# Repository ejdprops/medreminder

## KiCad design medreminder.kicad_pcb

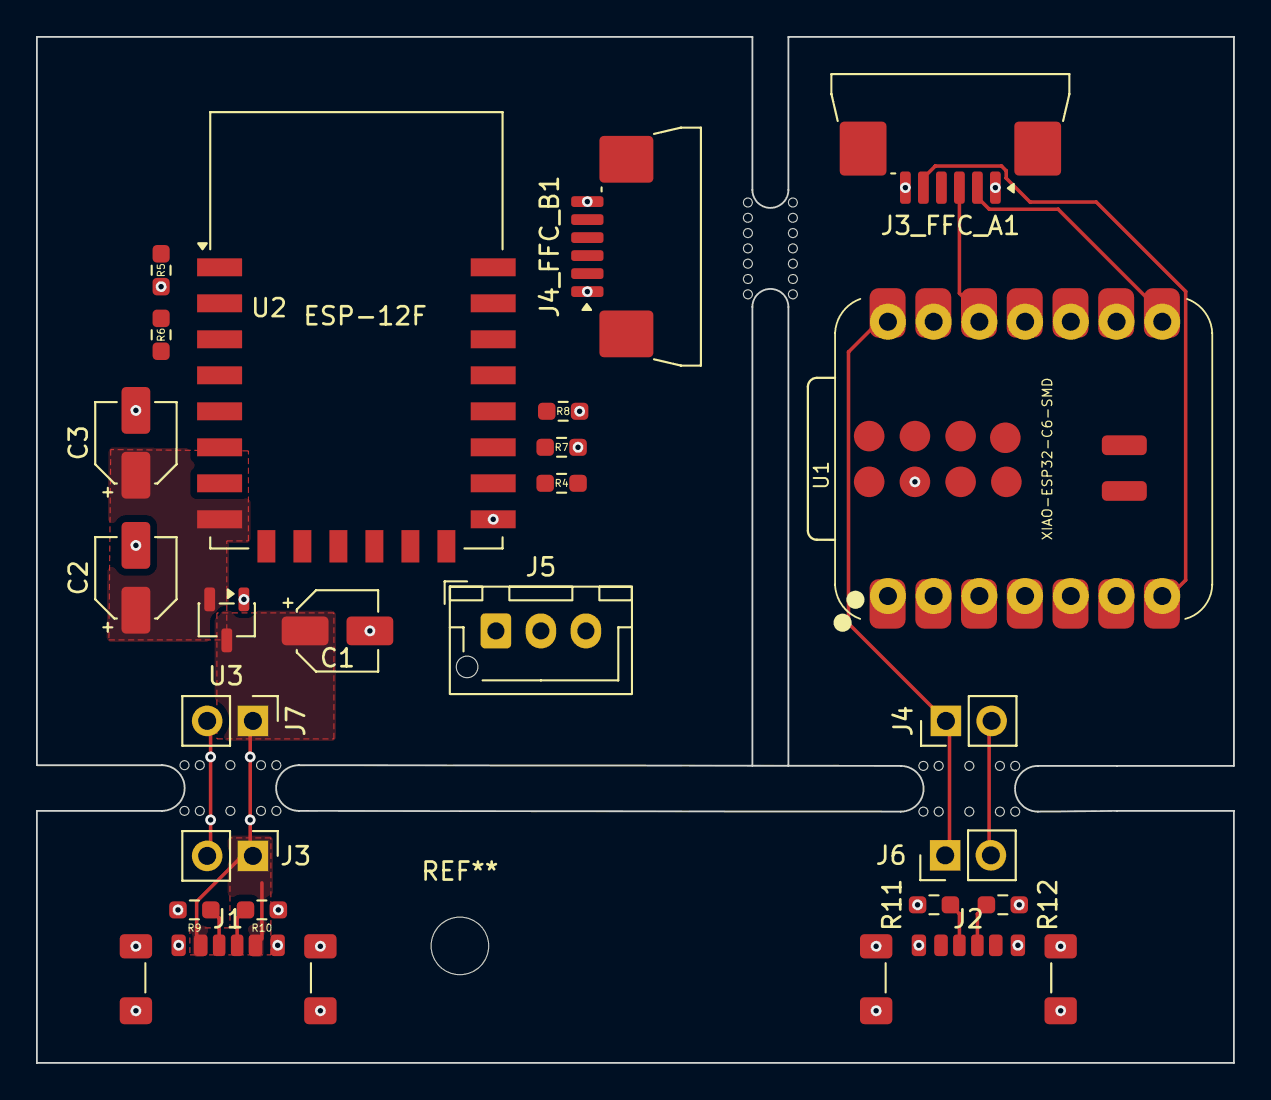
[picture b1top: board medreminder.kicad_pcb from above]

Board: 2 copper layers, 66.5 x 57.0 mm, 24 parts (0 on the bottom side), 16 nets.

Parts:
C1, C3: 10uF; CP_Elec_4x5.4
C2: 100nF; CP_Elec_4x5.4
J1: USB_C PWR XIAO (SNAP); USB_C_Receptacle_GCT_USB4135-GF-A_6P_TopMnt_Horizontal
J2: USB_C PWR ESP-12F (SNAP); USB_C_Receptacle_GCT_USB4135-GF-A_6P_TopMnt_Horizontal
J3: TO ESP-12F; PinHeader_1x02_P2.54mm_Vertical
J3_FFC_A1: FFC_CONN_12F; JUSHUO_AFA07-S06FCA-00_1x6-1MP_P1.0mm_Horizontal
J4: To XIAO; PinHeader_1x02_P2.54mm_Vertical
J4_FFC_B1: FFC_CONN_XIAO; JUSHUO_AFA07-S06FCA-00_1x6-1MP_P1.0mm_Horizontal
J5: LEDS; JST_XH_B3B-XH-AM_1x03_P2.50mm_Vertical
J6: To USB-C (XIAO); PinHeader_1x02_P2.54mm_Vertical
J7: TO USB-C (ESP); PinHeader_1x02_P2.54mm_Vertical
R4, R5, R6, R7, R8: 10k; R_0603_1608Metric_Pad0.98x0.95mm_HandSolder
R9, R10, R11, R12: 5.1k; R_0603_1608Metric_Pad0.98x0.95mm_HandSolder
U1: XIAO-ESP32-C6-SMD; XIAO-ESP32-C6-PTH-SMD
U2: ESP-12F; ESP-12E
U3: XC6206PxxxMR; SOT-23-3

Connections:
+3.3V: C2.1, C3.1, J3_FFC_A1.3, J4_FFC_B1.3, R4.1, U1.12 (3V3), U2.8 (VCC), U3.2 (VO)
+5V: C1.1, J1.A9 (VBUS), J1.B9 (VBUS), J2.A9 (VBUS), J2.B9 (VBUS), J3.1, J4.1, J5.1, J6.1, J7.1, U1.14 (VBUS), U3.3 (VI)
/<NO NET>: U1.1 (GPIO0_A0_D0), U1.2 (GPIO1_A1_D1), U1.3 (GPIO2_A2_D2), U1.4 (GPIO21_D3), U1.5 (GPIO22_D4_SDA), U1.6 (GPIO23_D5_SCL), U1.9 (GPIO19_D8_SCK), U1.10 (GPIO20_D9_MISO), U1.11 (GPIO18_D10_MOSI)
/EN: R6.2, U2.3 (EN)
/GPIO0: R8.2, U2.18 (GPIO0)
/GPIO2: R7.2, U2.17 (GPIO2)
/GPIO15: R4.2, U2.16 (GPIO15)
/LED_DATA: J5.3, U2.19 (GPIO4)
/RST: R5.2, U2.1 (~RST)
/UART_RX: J3_FFC_A1.2, J4_FFC_B1.2, U1.8 (GPIO17_D7_RX), U2.22 (GPIO1/TXD)
/UART_TX: J3_FFC_A1.5, J4_FFC_B1.5, U1.7 (GPIO16_D6_TX), U2.21 (GPIO3/RXD)
GND: C1.2, C2.2, C3.2, J1.A12 (GND), J1.B12 (GND), J1.SH (SHIELD), J2.A12 (GND), J2.B12 (GND), J2.SH (SHIELD), J3.2, J3_FFC_A1.1, J3_FFC_A1.6, J4.2, J4_FFC_B1.1, J4_FFC_B1.6, J5.2, J6.2, J7.2, R5.1, R6.1, R7.1, R8.1, R9.2, R10.1, R11.2, R12.1, U1.13 (GND), U1.27 (GND), U1.33 (GND), U2.15 (GND), U3.1 (GND)
unnamed: J1.A5 (CC1), R9.1
unnamed: J1.B5 (CC2), R10.2
unnamed: J2.A5 (CC1), R11.1
unnamed: J2.B5 (CC2), R12.2

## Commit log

2026-06-01 V1: Master board - XIAO C6 + ESP-12F, USB-C power, LED connector
2026-06-01 all updates
2026-06-01 add xiao pin-header footprint/3d file
2026-06-05 V2 tabled
2026-06-06 Add set_netclasses.py script for KiCad 10
2026-06-06 Remove embedded git repo
